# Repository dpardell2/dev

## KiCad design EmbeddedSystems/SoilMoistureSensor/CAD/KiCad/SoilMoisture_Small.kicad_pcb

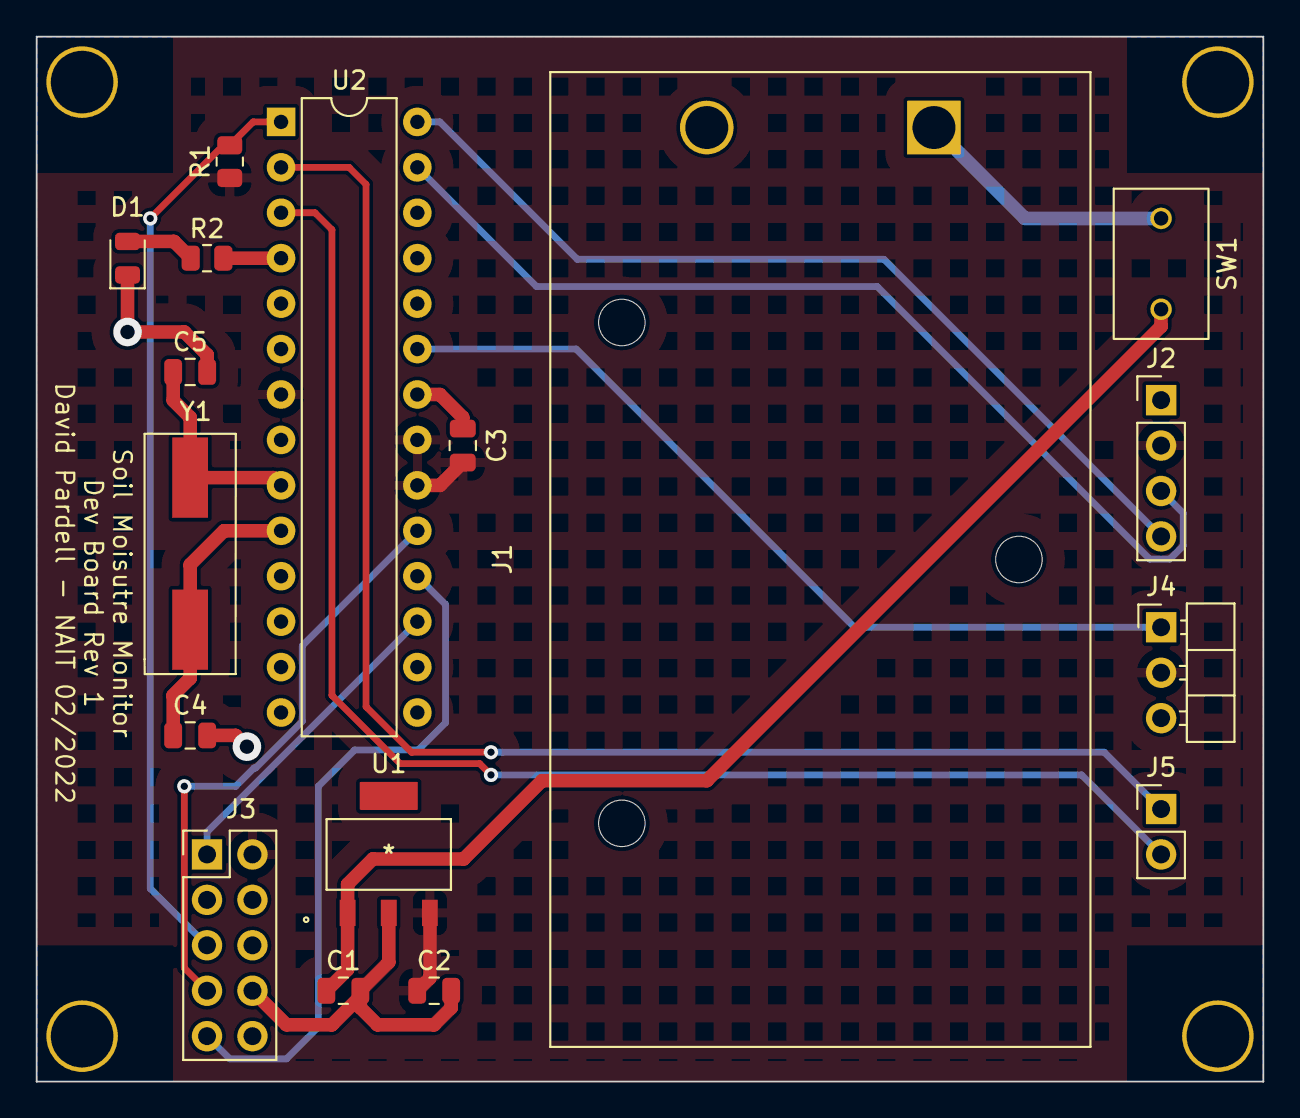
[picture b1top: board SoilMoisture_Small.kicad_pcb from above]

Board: 2 copper layers, 68.6 x 58.4 mm, 17 parts (0 on the bottom side), 17 nets.

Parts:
C1, C2: 1uF; C_0805_2012Metric
C3: 0.1uF; C_0805_2012Metric
C4, C5: 18pF; C_0805_2012Metric
D1: LED; LED_0805_2012Metric
J1: BH9VPC; BatteryHolder_Eagle_12BH611-GR
J2: LCD_I2C_Header; PinHeader_1x04_P2.54mm_Vertical
J3: AVR-ISP; PinHeader_2x05_P2.54mm_Vertical
J4: Moisture_Sensor_Header; PinHeader_1x03_P2.54mm_Horizontal
J5: TxRx; PinHeader_1x02_P2.54mm_Vertical
R1: 10k; R_0805_2012Metric
R2: 330; R_0805_2012Metric
SW1: SW_SPST; SPST
U1: MCP1755S-5002E/DB; MCP1755S-5002E&slash_DB
U2: ATmega328-P; DIP-28_W7.62mm
Y1: Crystal; Crystal_SMD_HC49-SD

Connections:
/9V: J1.1, SW1.2 (B)
GND: C1.2, C2.2, C3.2, C4.2, C5.2, D1.1 (K), J1.2, J2.1, J3.4, J3.6, J3.8, J3.10, J4.3, U1.2 (GND), U2.8 (GND), U2.22 (GND)
unnamed: C1.1, SW1.1 (A), U1.1 (VIN)
unnamed: C4.1, U2.10 (XTAL2/PB7), Y1.2
unnamed: C5.1, U2.9 (XTAL1/PB6), Y1.1
unnamed: D1.2 (A), R2.1
unnamed: J2.3, U2.27 (PC4)
unnamed: J2.4, U2.28 (PC5)
unnamed: J3.1, U2.17 (PB3)
unnamed: J3.5, R1.2, U2.1 (~RESET/PC6)
unnamed: J3.7, U2.19 (PB5)
unnamed: J3.9, U2.18 (PB4)
unnamed: J4.1, U2.23 (PC0)
unnamed: J5.1, U2.2 (PD0)
unnamed: J5.2, U2.3 (PD1)
unnamed: R2.2, U2.4 (PD2)
VCC: C2.1, C3.1, J2.2, J3.2, J4.2, R1.1, U1.3 (VOUT), U2.7 (VCC), U2.20 (AVCC), U2.21 (AREF)

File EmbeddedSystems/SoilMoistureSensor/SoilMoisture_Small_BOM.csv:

Date:,2/24/22 00:00,,,,,,,,,,,
Component Count:,,18,,,,,,,,,,
,,,,,,,,,,,,
Components:,,,,,,,,,,,,
,,,,,,,,,,,,
Item,Qty,Reference(s),Value,,,,Part Number,,,,,Footprint
1,2,"C1, C2",1uF,,,,CL21B105KAFNNNG,,,,,Capacitor_SMD:C_0805_2012Metric
2,1,C3,0.1uF,,,,160R15W104KV4T,,,,,Capacitor_SMD:C_0805_2012Metric
3,2,"C4, C5",18pF,,,,399-8030-1-ND,,,,,Capacitor_SMD:C_0805_2012Metric
4,1,D1,LED RED 0805 SMD,,,,LS R976-NR-1,,,,,LED_SMD:LED_0805_2012Metric
5,1,J1,BH9VPC,,,,BH9VPC,,,,,Battery:BatteryHolder_Eagle_12BH611-GR
6,2,"J2, J4, J5","PIN HEADER , THR, SINGLE ROW,.10",,,,PR20206VBNN,,,,,Connector_PinHeader_2.54mm:PinHeader_1x04_P2.54mm_Vertical
7,1,J3,PIN HEADER 2.54MM PITCH STR DIP,,,,G800LQ591018EU,,,,,Connector_PinHeader_2.54mm:PinHeader_2x05_P2.54mm_Vertical
8,1,R1,10k?,,,,Device:R_US,,,,,Resistor_SMD:R_0805_2012Metric
9,1,R2,330?,,,,Device:R_US,,,,,Resistor_SMD:R_0805_2012Metric
10,1,SW1,SW_SPST,,,,108-0047-EVX,,,,,SPST:SPST
11,1,U1,LDO 5V Regulator,,,,MCP1755S:MCP1755S-5002E{slash}DB,,,,,MCP1755S:MCP1755S-5002E&slash_DB
12,1,U2,ATmega328-P,,,,MCU_Microchip_ATmega:ATmega328-P,,,,,Package_DIP:DIP-28_W7.62mm
13,1,Y1,Crystal,,,,1923-830051235CT,,,,,Crystal:Crystal_SMD_HC49-SD
14,1,N/A,I2C LCD Module,,,,2004A-V1.1,,,,,N/A
15,1,N/A,9V Battery,,,,EN22,,,,,N/A
16,1,N/A,Soil Moisture Sensor,,,,EK1940,,,,,N/A
17,4,N/A,"HEX STANDOFF #4-40 ALUMINUM 1/2""",,,,2203,,,,,N/A
18,4,N/A,MACHINE SCREW PAN PHILLIPS 4-40,,,,PMSSS 440 0025 PH,,,,,N/A

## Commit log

2022-03-10 Removed redundant folder
2022-03-10 added KiCad Project and Gerbers for SoilMoistureMonitor
2022-03-10 removed backup files from KiCad proj

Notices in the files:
parts and their libraries:
Copyright 2021 Accelerated Designs. All rights reserved.
